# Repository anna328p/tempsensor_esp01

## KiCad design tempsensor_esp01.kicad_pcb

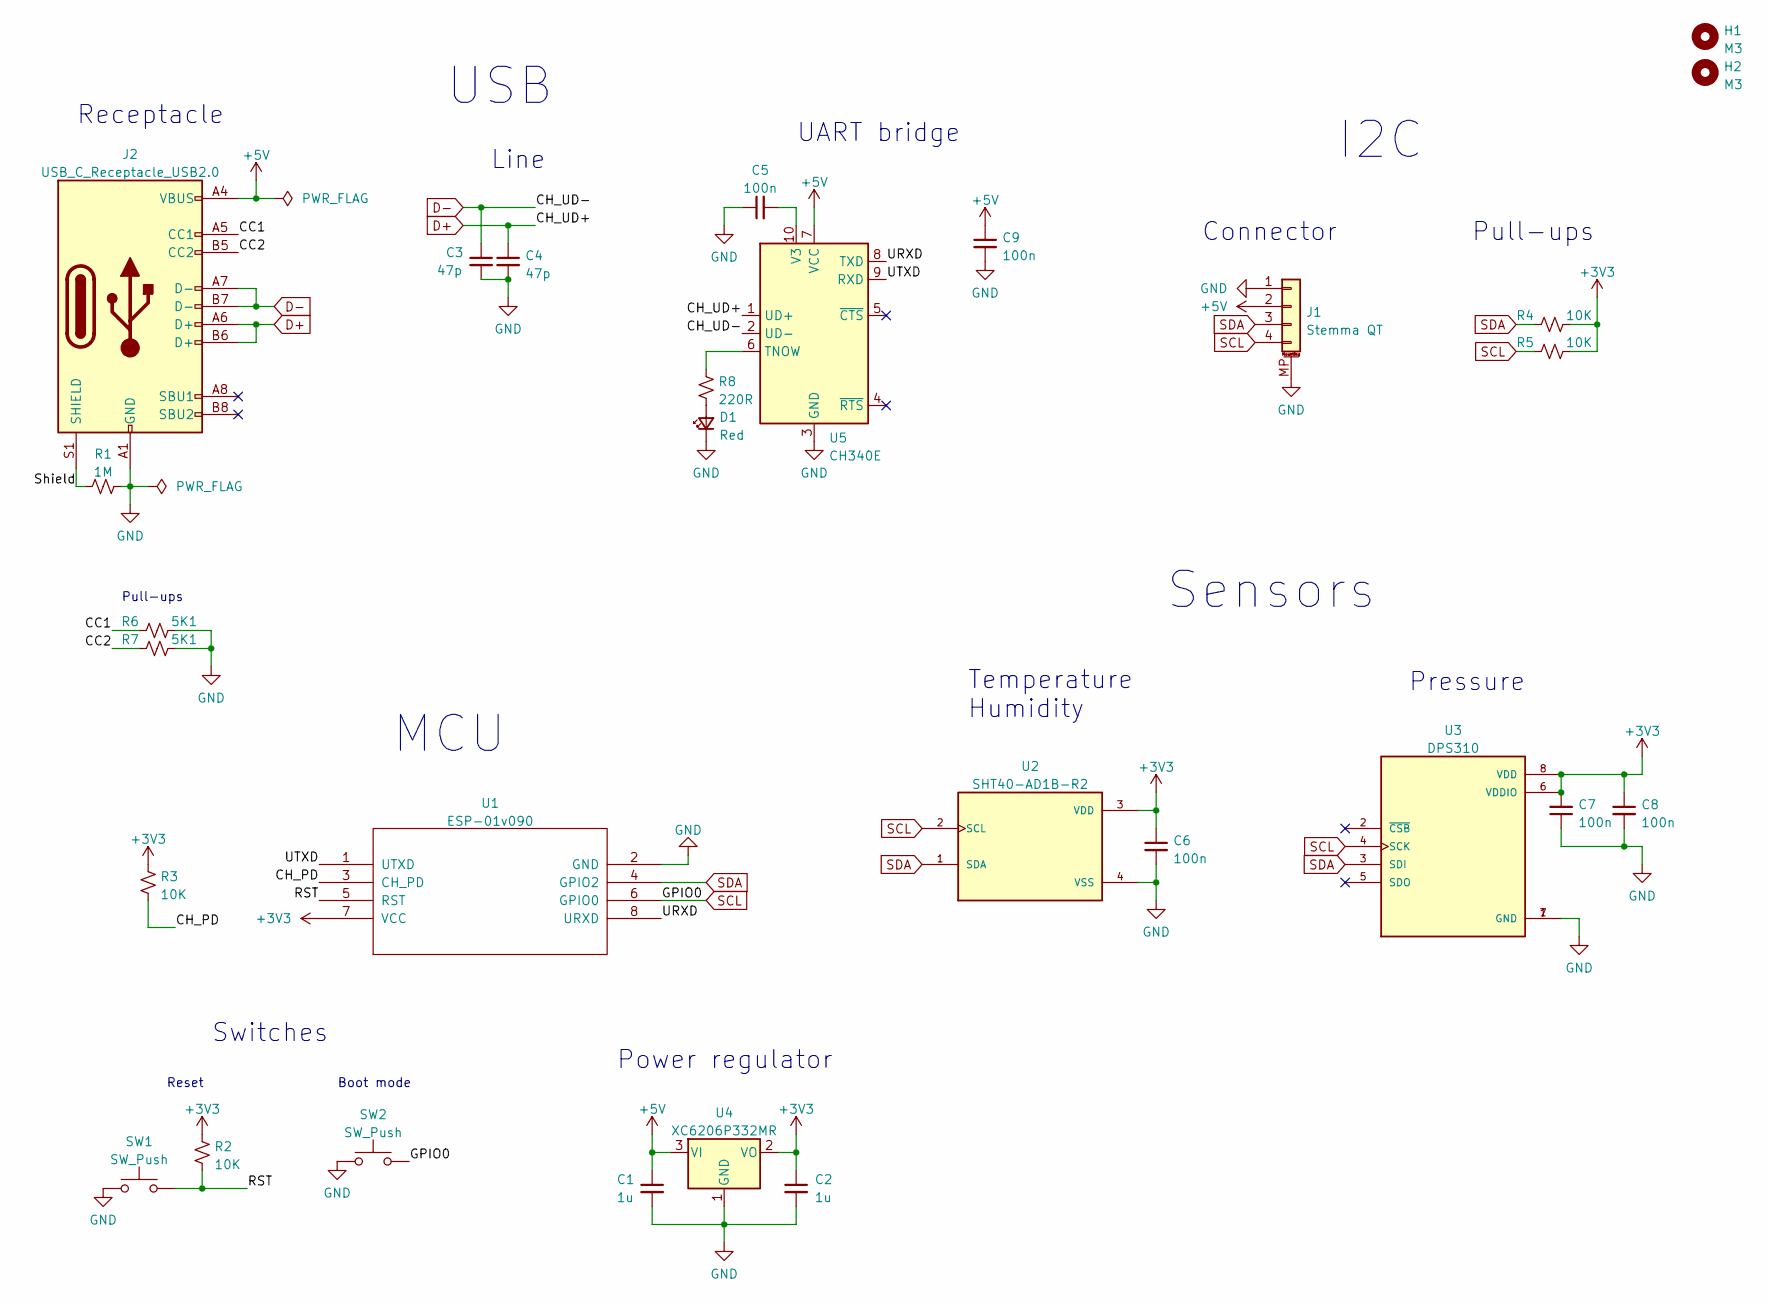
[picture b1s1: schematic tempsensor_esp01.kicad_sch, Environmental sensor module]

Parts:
C1, C2: 1u; C_0402_1005Metric; LCSC C52923
C3, C4: 47p; C_0402_1005Metric; LCSC C1567
C5, C6, C7, C8, C9: 100n; C_0402_1005Metric; LCSC C1525
D1: Red; LED_0603_1608Metric; LCSC C2286
H1, H2: M3; MountingHole_3.2mm_M3
J1: Stemma QT; JST_SH_SM04B-SRSS-TB_1x04-1MP_P1.00mm_Horizontal; LCSC C160404
J2: USB_C_Receptacle_USB2.0; USB_C_Receptacle_HRO_TYPE-C-31-M-12; LCSC C165948
R1: 1M; R_0402_1005Metric; LCSC C26083
R2, R3, R4, R5: 10K; R_0402_1005Metric; LCSC C25744
R6, R7: 5K1; R_0402_1005Metric; LCSC C25905
R8: 220R; R_0402_1005Metric; LCSC C25091
SW1, SW2: SW_Push; SW_Push_SPST_NO_Alps_SKRK; LCSC C115357
U1: ESP-01v090; ESP-01; LCSC C503582
U2: SHT40-AD1B-R2; XDCR_SHT40-AD1B-R2; LCSC C2909890
U3: DPS310; XDCR_DPS310; LCSC C130156
U4: XC6206P332MR; SOT-23; LCSC C5446
U5: CH340E; MSOP-10_3x3mm_P0.5mm; LCSC C99652

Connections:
+3V3: C2.1, C6.1, C7.2, C8.1, R2.1, R3.1, R4.2, R5.2, U1.7 (VCC), U2.3 (VDD), U3.6 (VDDIO), U3.8 (VDD), U4.2 (VO)
+5V: C1.1, C9.1, J1.2, J2.A4 (VBUS), J2.A9 (VBUS), J2.B4 (VBUS), J2.B9 (VBUS), U4.3 (VI), U5.7 (VCC)
/CC1: J2.A5 (CC1), R6.1
/CC2: J2.B5 (CC2), R7.2
/CH_PD: R3.2, U1.3 (CH_PD)
/RST: R2.2, SW1.2, U1.5 (RST)
/Shield: J2.S1 (SHIELD), R1.2
/URXD: U1.8 (URXD), U5.8 (TXD)
/UTXD: U1.1 (UTXD), U5.9 (RXD)
D+: C4.1, J2.A6 (D+), J2.B6 (D+), U5.1 (UD+)
D-: C3.1, J2.A7 (D-), J2.B7 (D-), U5.2 (UD-)
GND: C1.2, C2.2, C3.2, C4.2, C5.1, C6.2, C7.1, C8.2, C9.2, D1.1 (K), J1.1, J1.MP (MountPin), J2.A1 (GND), J2.A12 (GND), J2.B1 (GND), J2.B12 (GND), R1.1, R6.2, R7.1, SW1.1, SW2.1, U1.2 (GND), U2.4 (VSS), U3.1 (GND), U3.7 (GND), U4.1 (GND), U5.3 (GND)
unnamed: C5.2, U5.10 (V3)
unnamed: D1.2 (A), R8.2
unnamed: R8.1, U5.6 (TNOW)
SCL: J1.4, R5.1, SW2.2, U1.6 (GPIO0), U2.2 (SCL), U3.4 (SCK)
SDA: J1.3, R4.1, U1.4 (GPIO2), U2.1 (SDA), U3.3 (SDI)

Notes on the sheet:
Line
Sensors
Reset
UART bridge
Receptacle
Temperature Humidity
USB
Connector
Boot mode
Switches
Power regulator
Pull-ups
MCU
Pressure
I2C

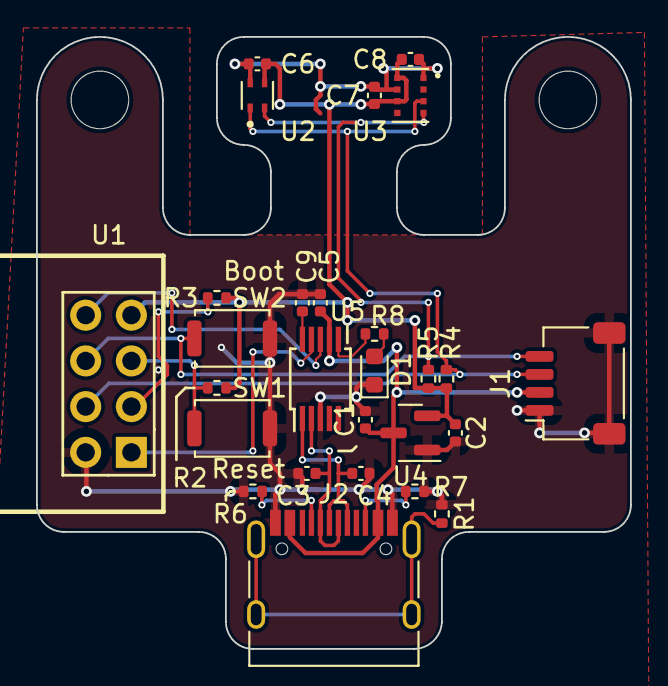
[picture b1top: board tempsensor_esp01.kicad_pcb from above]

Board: 2 copper layers, 33.0 x 34.0 mm, 29 parts (0 on the bottom side), 17 nets.

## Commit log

2022-11-16 add esp8266 module
2022-11-16 complete schematic
2022-11-18 complete board
2022-11-18 generate out files
2022-11-18 fix library
2022-11-18 add script
2022-11-18 fix silkscreen
2022-11-18 redesign using CH340E
2022-11-19 change power regulator
